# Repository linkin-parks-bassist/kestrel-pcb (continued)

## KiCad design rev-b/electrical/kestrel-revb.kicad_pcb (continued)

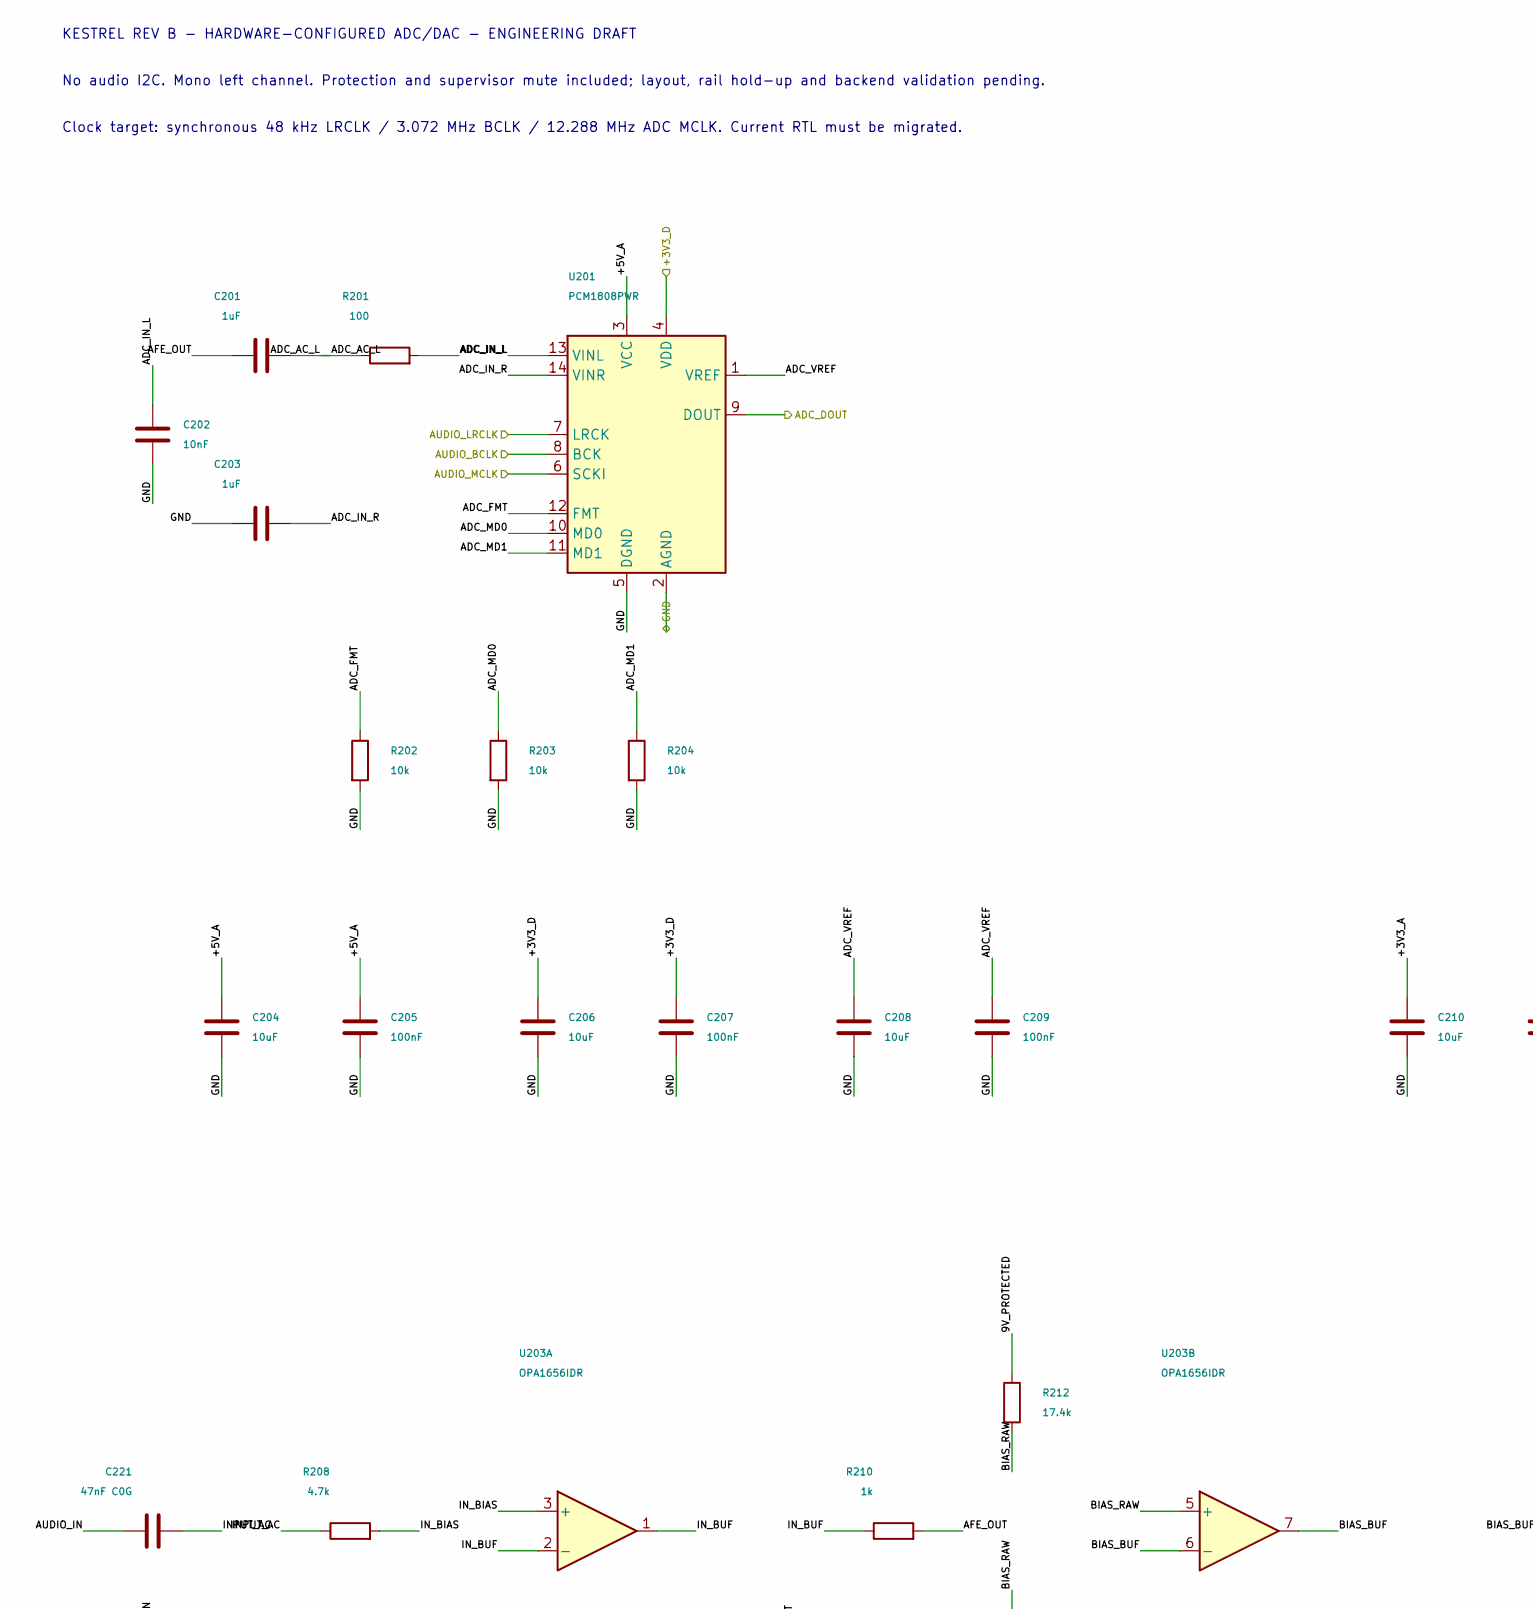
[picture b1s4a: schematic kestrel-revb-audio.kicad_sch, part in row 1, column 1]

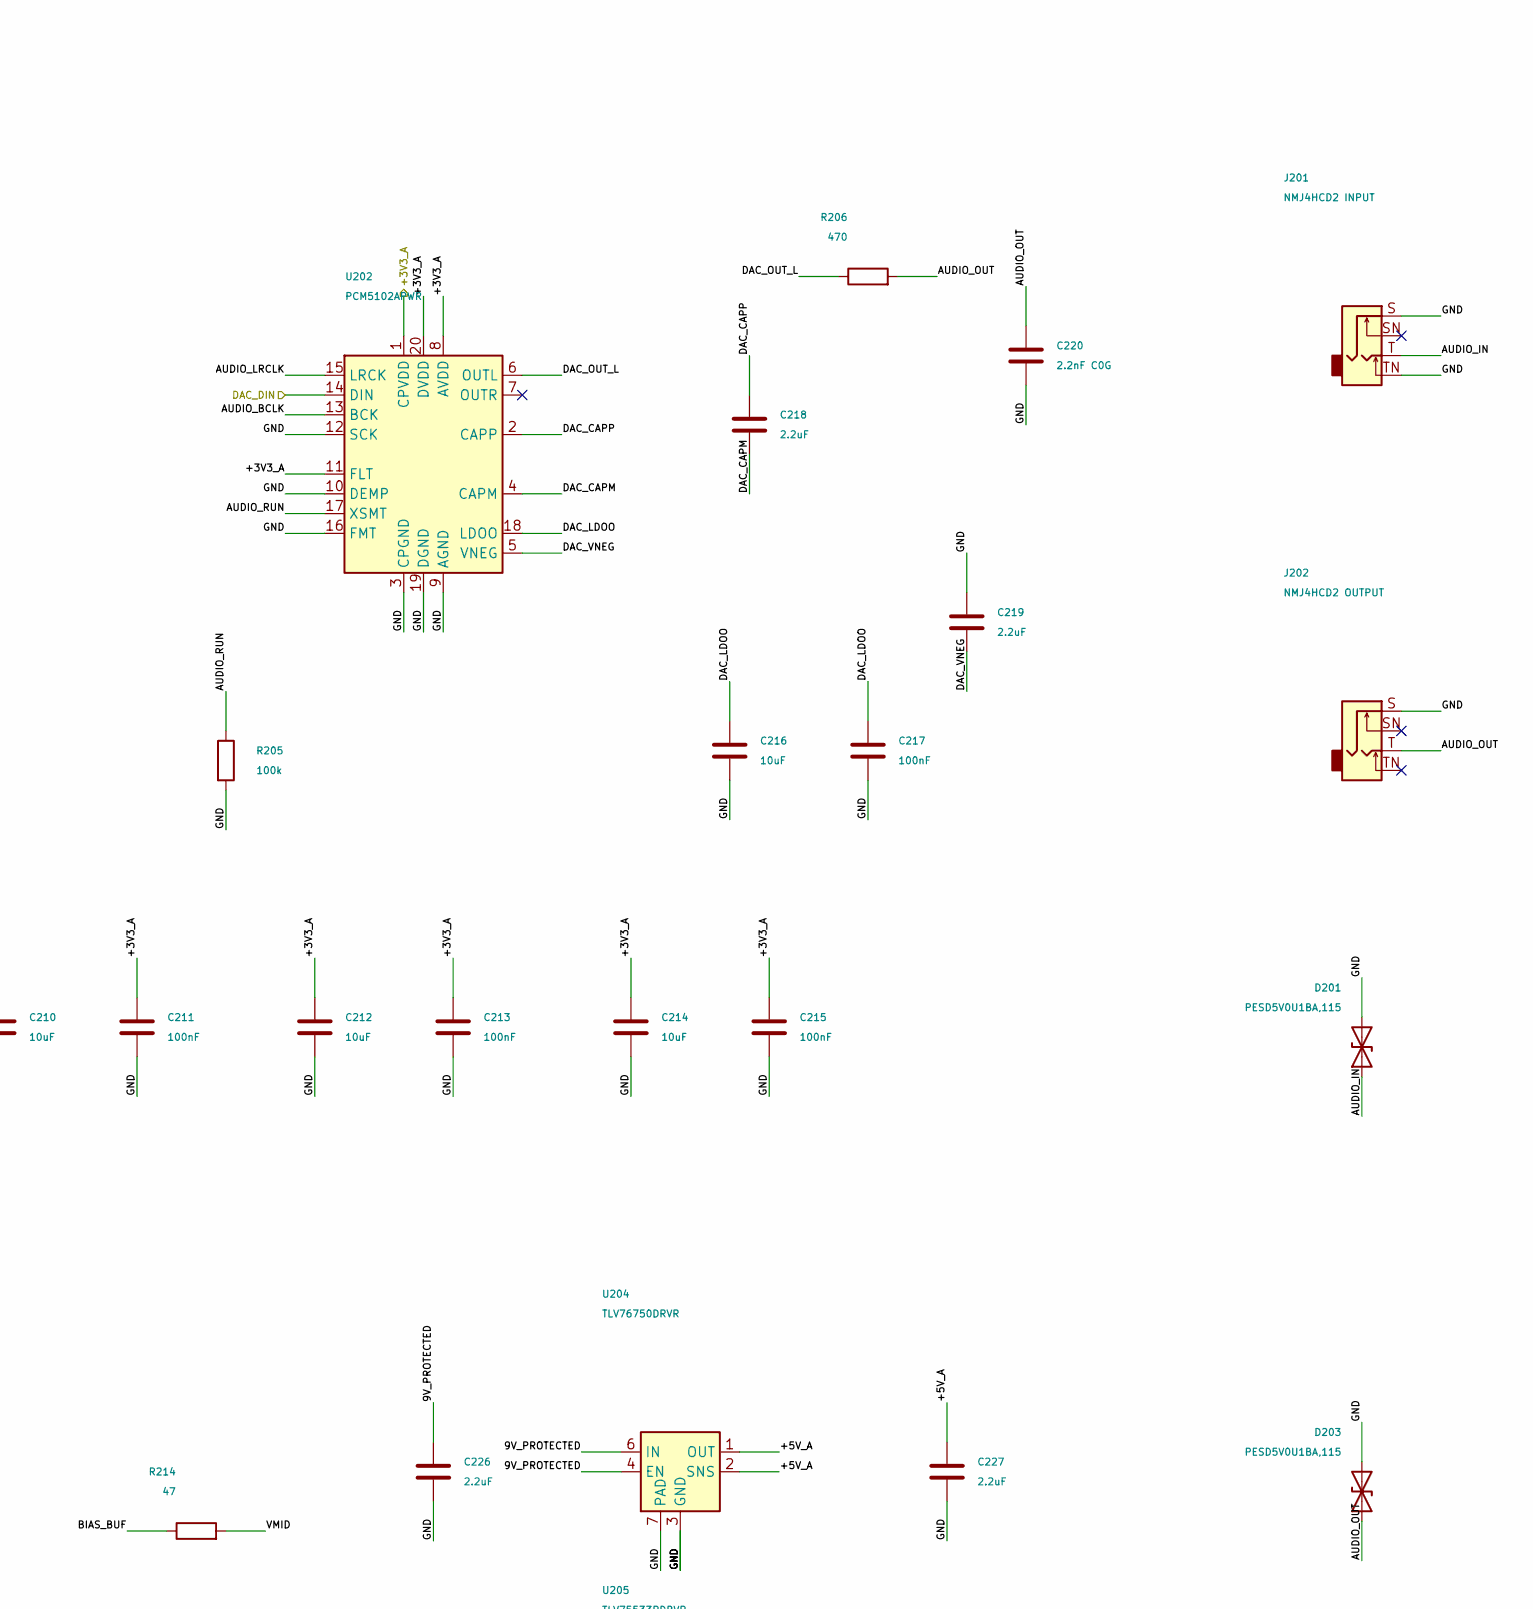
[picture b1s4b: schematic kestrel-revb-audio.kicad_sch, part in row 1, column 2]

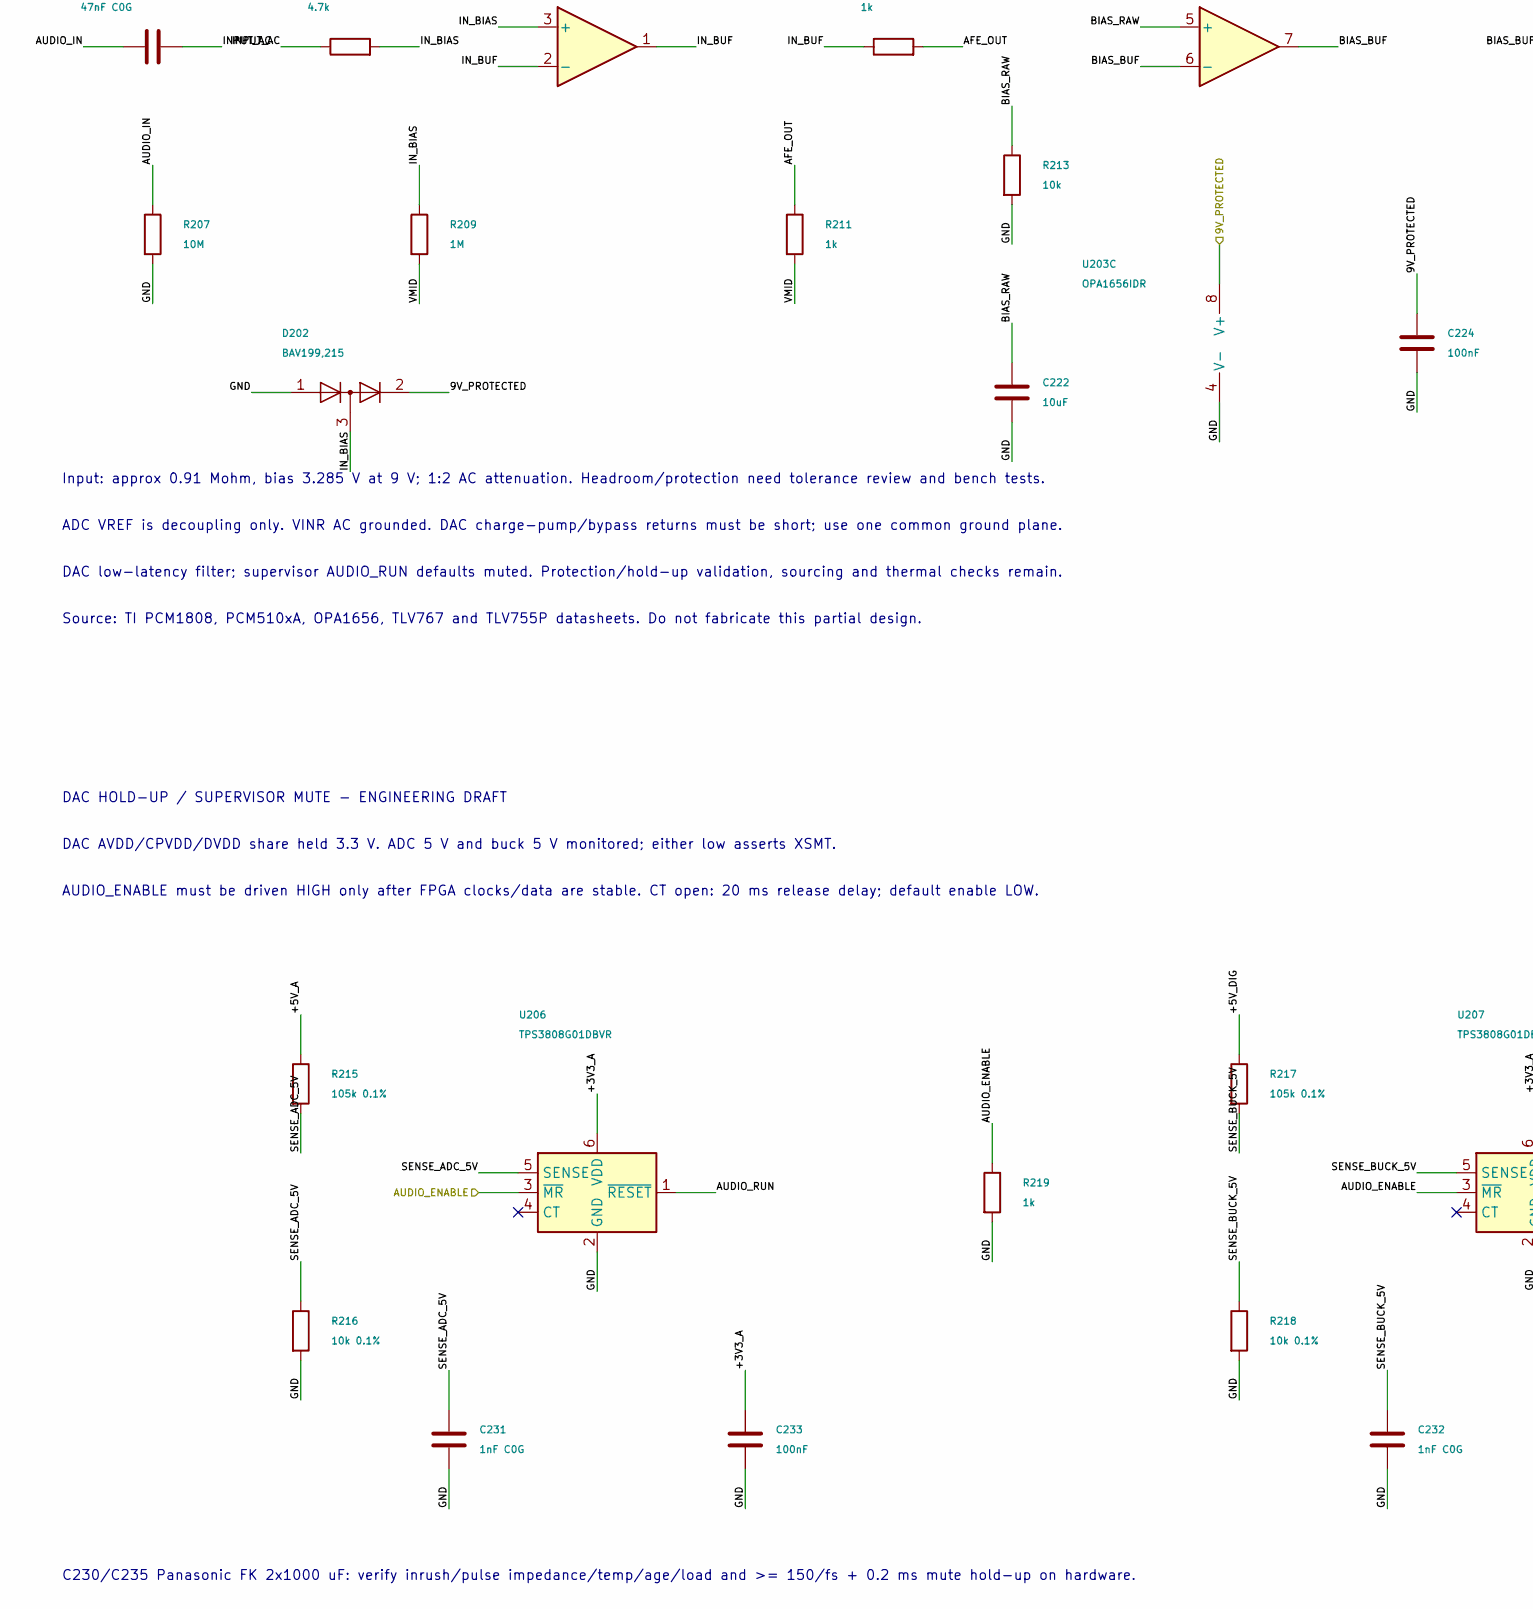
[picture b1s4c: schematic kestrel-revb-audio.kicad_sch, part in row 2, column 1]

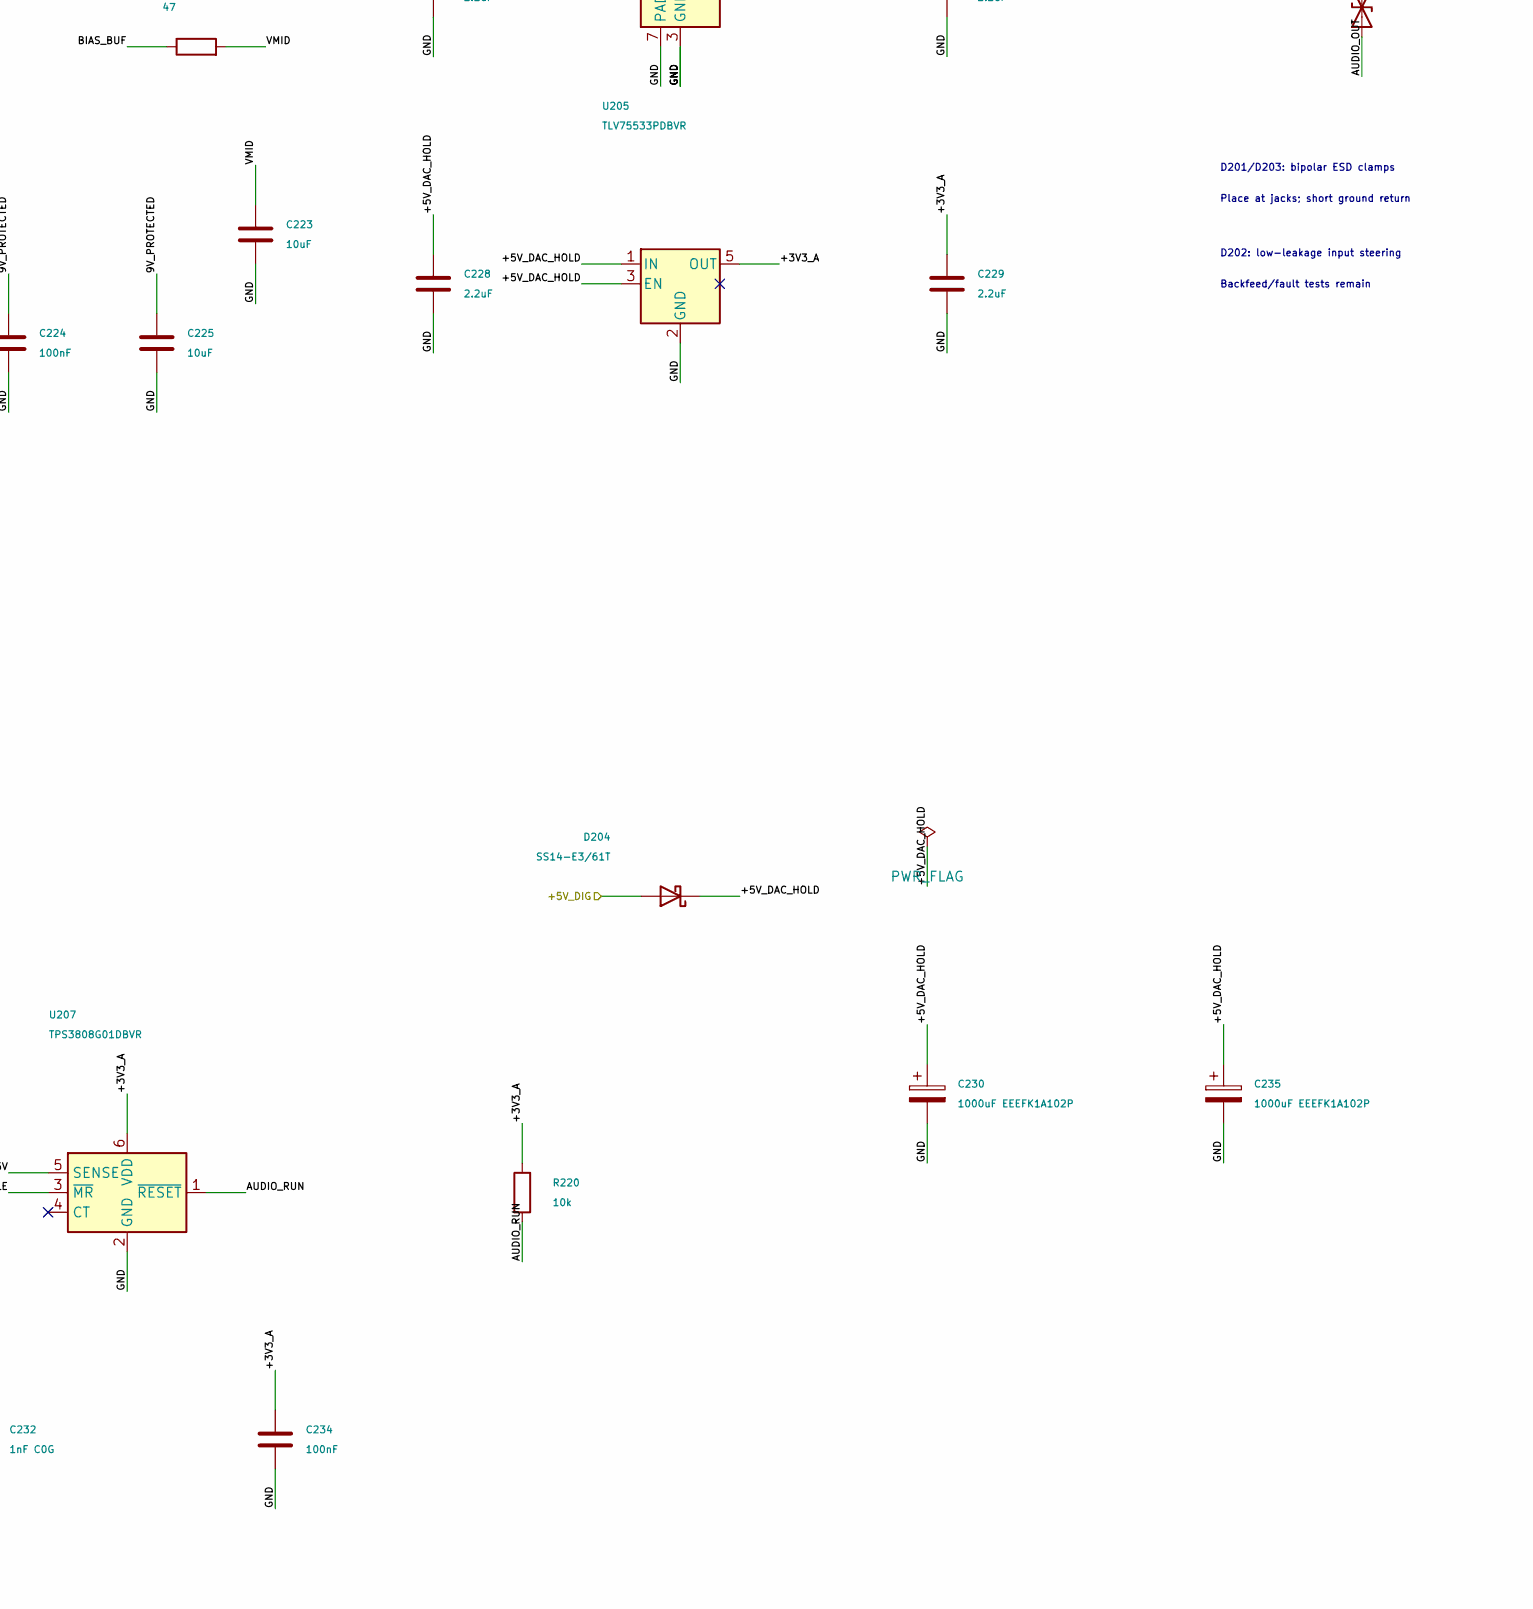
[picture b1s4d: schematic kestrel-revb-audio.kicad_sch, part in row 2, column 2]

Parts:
C201, C203: 1uF; C_0805_2012Metric; Rating 16 V minimum; bulk effective capacitanc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
C202: 10nF; C_0603_1608Metric; Rating 16 V minimum; bulk effective capacitanc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
C204, C206, C208, C210, C212, C214, C216, C222, C223, C225: 10uF; C_0805_2012Metric; Rating 16 V minimum; bulk effective capacitanc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
C205, C207, C209, C211, C213, C215, C217, C224, C233, C234: 100nF; C_0603_1608Metric; Rating 16 V minimum; bulk effective capacitanc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
C218, C219, C226, C227, C228, C229: 2.2uF; C_0805_2012Metric; Rating 16 V minimum; bulk effective capacitanc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
C220: 2.2nF C0G; C_0603_1608Metric; Rating 16 V minimum; bulk effective capacitanc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
C221: 47nF C0G; C_1206_3216Metric; Rating 50 V C0G; input transient barrier
C230, C235: 1000uF EEEFK1A102P; CP_Elec_Panasonic_FK_G_10x10.2; Rating 10 V; +/-20 percent at 20 C; 2000 h at 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; MPN EEEFK1A102P; LCSC C278397
C231, C232: 1nF C0G; C_0603_1608Metric; Rating 16 V minimum; bulk effective capacitanc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
D201, D203: PESD5V0U1BA,115; D_SOD-323
D202: BAV199,215; SOT-23
D204: SS14-E3/61T; D_SMA
J201: NMJ4HCD2 INPUT; Jack_6.35mm_Neutrik_NMJ4HCD2_Horizontal
J202: NMJ4HCD2 OUTPUT; Jack_6.35mm_Neutrik_NMJ4HCD2_Horizontal
R201: 100; R_0603_1608Metric
R202, R203, R204, R213, R220: 10k; R_0603_1608Metric
R205: 100k; R_0603_1608Metric
R206: 470; R_0603_1608Metric
R207: 10M; R_0603_1608Metric
R208: 4.7k; R_1206_3216Metric; Rating 1 percent; 0.25 W minimum; pulse rating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
R209: 1M; R_0603_1608Metric
R210, R211, R219: 1k; R_0603_1608Metric
R212: 17.4k; R_0603_1608Metric
R214: 47; R_0603_1608Metric
R215, R217: 105k 0.1%; R_0603_1608Metric
R216, R218: 10k 0.1%; R_0603_1608Metric
U201: PCM1808PWR; TSSOP-14_4.4x5mm_P0.65mm
U202: PCM5102APWR; TSSOP-20_4.4x6.5mm_P0.65mm
U203: OPA1656IDR; SOIC-8_3.9x4.9mm_P1.27mm
U204: TLV76750DRVR; WSON-6-1EP_2x2mm_P0.65mm_EP1x1.6mm_ThermalVias
U205: TLV75533PDBVR; SOT-23-5
U206, U207: TPS3808G01DBVR; SOT-23-6

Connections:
/9V_PROTECTED: C224.1, C225.1, C226.1, D202.2 (K2), R212.1, U203.8 (V+), U204.4 (EN), U204.6 (IN); also elsewhere on the board
/+3V3_A: C210.1, C211.1, C212.1, C213.1, C214.1, C215.1, C229.1, C233.1, C234.1, R220.1, U202.1 (CPVDD), U202.8 (AVDD), U202.11 (FLT), U202.20 (DVDD), U205.5 (OUT), U206.6 (VDD), U207.6 (VDD); also elsewhere on the board
/+3V3_D: C206.1, C207.1, U201.4 (VDD); also elsewhere on the board
/+5V_DIG: D204.2 (A), R217.1; also elsewhere on the board
/ADC_DOUT: U201.9 (DOUT); also elsewhere on the board
/AUDIO_BCLK: U201.8 (BCK), U202.13 (BCK); also elsewhere on the board
/AUDIO_ENABLE: R219.1, U206.3 (~MR), U207.3 (~MR); also elsewhere on the board
/AUDIO_LRCLK: U201.7 (LRCK), U202.15 (LRCK); also elsewhere on the board
/AUDIO_MCLK: U201.6 (SCKI); also elsewhere on the board
/DAC_DIN: U202.14 (DIN); also elsewhere on the board
/GND: C202.2, C203.1, C204.2, C205.2, C206.2, C207.2, C208.2, C209.2, C210.2, C211.2, C212.2, C213.2, C214.2, C215.2, C216.2, C217.2, C219.1, C220.2, C222.2, C223.2, C224.2, C225.2, C226.2, C227.2, C228.2, C229.2, C230.2, C231.2, C232.2, C233.2, C234.2, C235.2, D201.2 (A2), D202.1 (A1), D203.2 (A2), J201.S, J201.TN, J202.S, R202.2, R203.2, R204.2, R205.2, R207.2, R213.2, R216.2, R218.2, R219.2, U201.2 (AGND), U201.5 (DGND), U202.3 (CPGND), U202.9 (AGND), U202.10 (DEMP), U202.12 (SCK), U202.16 (FMT), U202.19 (DGND), U203.4 (V-), U204.3 (GND), U204.5 (GND), U204.7 (PAD), U205.2 (GND), U206.2 (GND), U207.2 (GND); also elsewhere on the board
/Hardware ADC and DAC/+5V_A: C204.1, C205.1, C227.1, R215.1, U201.3 (VCC), U204.1 (OUT), U204.2 (SNS)
/Hardware ADC and DAC/+5V_DAC_HOLD: C228.1, C230.1, C235.1, D204.1 (K), U205.1 (IN), U205.3 (EN)
/Hardware ADC and DAC/ADC_AC_L: C201.2, R201.1
/Hardware ADC and DAC/ADC_FMT: R202.1, U201.12 (FMT)
/Hardware ADC and DAC/ADC_IN_L: C202.1, R201.2, U201.13 (VINL)
/Hardware ADC and DAC/ADC_IN_R: C203.2, U201.14 (VINR)
/Hardware ADC and DAC/ADC_MD0: R203.1, U201.10 (MD0)
/Hardware ADC and DAC/ADC_MD1: R204.1, U201.11 (MD1)
/Hardware ADC and DAC/ADC_VREF: C208.1, C209.1, U201.1 (VREF)
/Hardware ADC and DAC/AFE_OUT: C201.1, R210.2, R211.1
/Hardware ADC and DAC/AUDIO_IN: C221.1, D201.1 (A1), J201.T, R207.1
/Hardware ADC and DAC/AUDIO_OUT: C220.1, D203.1 (A1), J202.T, R206.2
/Hardware ADC and DAC/AUDIO_RUN: R205.1, R220.2, U202.17 (XSMT), U206.1 (~RESET), U207.1 (~RESET)
/Hardware ADC and DAC/BIAS_BUF: R214.1, U203.6 (-), U203.7
/Hardware ADC and DAC/BIAS_RAW: C222.1, R212.2, R213.1, U203.5 (+)
/Hardware ADC and DAC/DAC_CAPM: C218.2, U202.4 (CAPM)
/Hardware ADC and DAC/DAC_CAPP: C218.1, U202.2 (CAPP)
/Hardware ADC and DAC/DAC_LDOO: C216.1, C217.1, U202.18 (LDOO)
/Hardware ADC and DAC/DAC_OUT_L: R206.1, U202.6 (OUTL)
/Hardware ADC and DAC/DAC_VNEG: C219.2, U202.5 (VNEG)
/Hardware ADC and DAC/INPUT_AC: C221.2, R208.1
/Hardware ADC and DAC/IN_BIAS: D202.3 (K1/A2), R208.2, R209.1, U203.3 (+)
/Hardware ADC and DAC/IN_BUF: R210.1, U203.1, U203.2 (-)
/Hardware ADC and DAC/SENSE_ADC_5V: C231.1, R215.2, R216.1, U206.5 (SENSE)
/Hardware ADC and DAC/SENSE_BUCK_5V: C232.1, R217.2, R218.1, U207.5 (SENSE)
/Hardware ADC and DAC/VMID: C223.1, R209.2, R211.2, R214.2

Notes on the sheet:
KESTREL REV B - HARDWARE-CONFIGURED ADC/DAC - ENGINEERING DRAFT
No audio I2C. Mono left channel. Protection and supervisor mute included; layout, rail hold-up and backend validation pending.
Clock target: synchronous 48 kHz LRCLK / 3.072 MHz BCLK / 12.288 MHz ADC MCLK. Current RTL must be migrated.
Input: approx 0.91 Mohm, bias 3.285 V at 9 V; 1:2 AC attenuation. Headroom/protection need tolerance review and bench tests.
ADC VREF is decoupling only. VINR AC grounded. DAC charge-pump/bypass returns must be short; use one common ground plane.
DAC low-latency filter; supervisor AUDIO_RUN defaults muted. Protection/hold-up validation, sourcing and thermal checks remain.
Source: TI PCM1808, PCM510xA, OPA1656, TLV767 and TLV755P datasheets. Do not fabricate this partial design.
D201/D203: bipolar ESD clamps
Place at jacks; short ground return
D202: low-leakage input steering
Backfeed/fault tests remain
DAC HOLD-UP / SUPERVISOR MUTE - ENGINEERING DRAFT
DAC AVDD/CPVDD/DVDD share held 3.3 V. ADC 5 V and buck 5 V monitored; either low asserts XSMT.
AUDIO_ENABLE must be driven HIGH only after FPGA clocks/data are stable. CT open: 20 ms release delay; default enable LOW.
C230/C235 Panasonic FK 2x1000 uF: verify inrush/pulse impedance/temp/age/load and >= 150/fs + 0.2 ms mute hold-up on hardware.

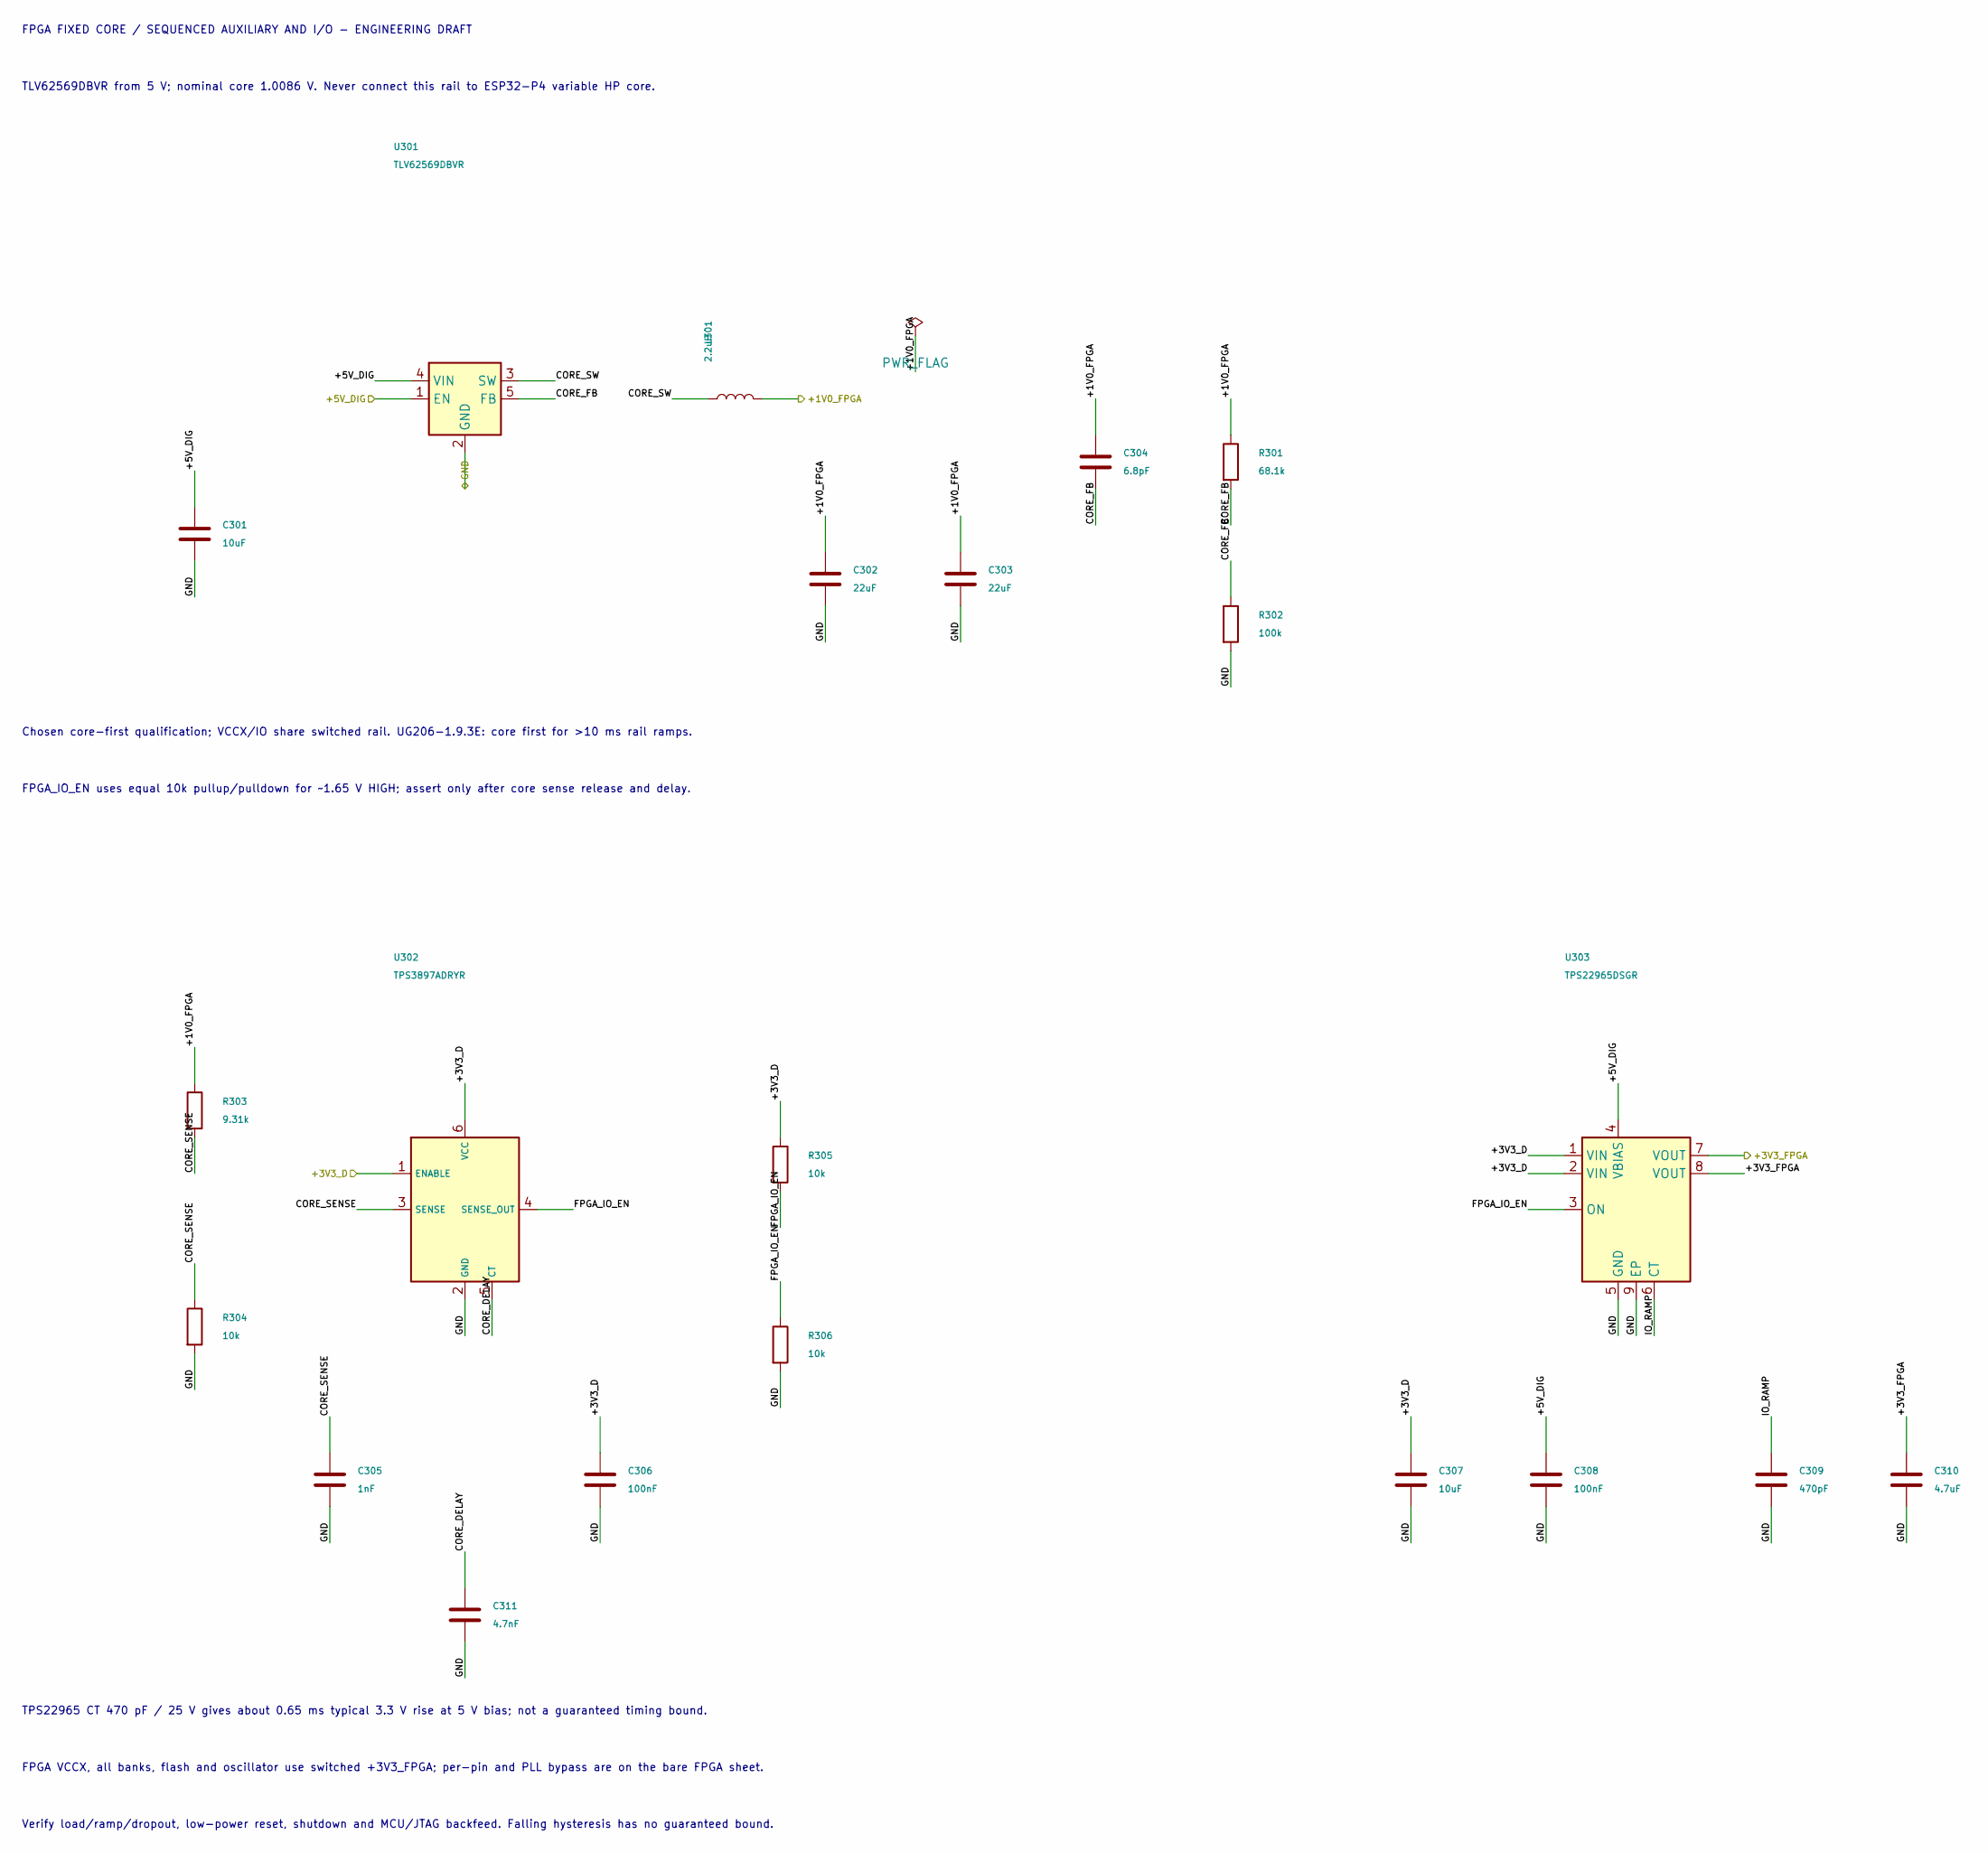
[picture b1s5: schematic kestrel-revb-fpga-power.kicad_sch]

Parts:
C301, C307: 10uF; C_1210_3225Metric; Rating 10uF / 16V X7R
C302, C303: 22uF; C_1210_3225Metric; Rating 22uF / 16V X7R
C304: 6.8pF; C_0603_1608Metric; Rating 6.8pF / C0G
C305: 1nF; C_0603_1608Metric; Rating 1nF / C0G
C306, C308: 100nF; C_0603_1608Metric; Rating 100nF / 16V
C309: 470pF; C_0603_1608Metric; Rating 470pF / 25V C0G
C310: 4.7uF; C_1210_3225Metric; Rating 4.7uF / 16V X7R
C311: 4.7nF; C_0603_1608Metric; Rating 4.7nF / 5% / 25V C0G
L301: 2.2uH; L_Sunlord_MWSA0402S; Rating 2.2uH / shielded / Isat >=3.5A; MPN MWSA0402S-2R2MT; LCSC C408335
R301: 68.1k; R_0603_1608Metric; Rating 68.1k / 0.1%
R302: 100k; R_0603_1608Metric; Rating 100k / 0.1%
R303: 9.31k; R_0603_1608Metric; Rating 9.31k / 0.1%
R304: 10k; R_0603_1608Metric; Rating 10k / 0.1%
R305, R306: 10k; R_0603_1608Metric; Rating 10k / 1%
U301: TLV62569DBVR; SOT-23-5
U302: TPS3897ADRYR; Texas_USON-6_1x1.45mm_P0.5mm_SMD
U303: TPS22965DSGR; TPS22965_DSG8_2x2

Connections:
/+1V0_FPGA: C302.1, C303.1, C304.1, L301.2, R301.1, R303.1; also elsewhere on the board
/+3V3_D: C306.1, C307.1, R305.1, U302.1 (ENABLE), U302.6 (VCC), U303.1 (VIN), U303.2 (VIN); also elsewhere on the board
/+3V3_FPGA: C310.1, U303.7 (VOUT), U303.8 (VOUT); also elsewhere on the board
/+5V_DIG: C301.1, C308.1, U301.1 (EN), U301.4 (VIN), U303.4 (VBIAS); also elsewhere on the board
/FPGA core and I/O sequencing/CORE_DELAY: C311.1, U302.5 (CT)
/FPGA core and I/O sequencing/CORE_FB: C304.2, R301.2, R302.1, U301.5 (FB)
/FPGA core and I/O sequencing/CORE_SENSE: C305.1, R303.2, R304.1, U302.3 (SENSE)
/FPGA core and I/O sequencing/CORE_SW: L301.1, U301.3 (SW)
/FPGA core and I/O sequencing/FPGA_IO_EN: R305.2, R306.1, U302.4 (SENSE_OUT), U303.3 (ON)
/FPGA core and I/O sequencing/IO_RAMP: C309.1, U303.6 (CT)
/GND: C301.2, C302.2, C303.2, C305.2, C306.2, C307.2, C308.2, C309.2, C310.2, C311.2, R302.2, R304.2, R306.2, U301.2 (GND), U302.2 (GND), U303.5 (GND), U303.9 (EP); also elsewhere on the board

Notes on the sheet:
FPGA FIXED CORE / SEQUENCED AUXILIARY AND I/O - ENGINEERING DRAFT
TLV62569DBVR from 5 V; nominal core 1.0086 V. Never connect this rail to ESP32-P4 variable HP core.
Chosen core-first qualification; VCCX/IO share switched rail. UG206-1.9.3E: core first for >10 ms rail ramps.
FPGA_IO_EN uses equal 10k pullup/pulldown for ~1.65 V HIGH; assert only after core sense release and delay.
TPS22965 CT 470 pF / 25 V gives about 0.65 ms typical 3.3 V rise at 5 V bias; not a guaranteed timing bound.
FPGA VCCX, all banks, flash and oscillator use switched +3V3_FPGA; per-pin and PLL bypass are on the bare FPGA sheet.
Verify load/ramp/dropout, low-power reset, shutdown and MCU/JTAG backfeed. Falling hysteresis has no guaranteed bound.
